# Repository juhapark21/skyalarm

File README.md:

# Sky Alarm
The sky alarm from xkcd #2979! It tells you when cool space things are happening. 

## Why 

I also wanted this device. There are alert apps and telegram groups and RSS feeds out there, but I wanted something not tied to my phone or computer. I also thought it would be fun to make a large physical device in the style of the original comic. 

## Features 
- Siren turns on (sound and light) when a cool space thing is happening in your location 
- Only alerts for phenomena observable with the naked eye 
- Cool space things:
  - Lunar eclipses
  - Solar eclipses
  - Supermoons
  - ISS passes
- Configurable notification settings 

## Usage 
2. Strip a cable (USB-C to USB-C or USB-A to USB-C; if using the latter, strip the USB-C end).
3. Locate the power and ground cables.
4. Secure the power and ground cables to their corresponding screw terminals (labeled on the PCB).
5. Get two lengths of wire. Connect one end of each wire to the battery terminals of the siren. (You may need to disassemble or drill into the casing to access this)
6. Connect the remaining end of each wire to the siren screw terminals (labeled on the PCB).
7. Put in separate batteries for the siren. Make sure the switch is turned ON.
8. Plug in any USB-C to USB-C wall charger to the XIAO ESP32C3.
9. Plug in the external power cable. 

## Specifications 
- XIAO ESP32C3 microcontroller - edit firmware without any extra equipment
- MAX98357A - cheap and widely available amplifier 
- Any toy siren ~5V with an on-off switch and batteries should work
- 61.4 x 65.5 mm PCB - casing can be made smaller with different parts without adjusting the board
- Runs on any wall power supply 1A-3A (suggested) 
- bom can be found as bom.csv 

## Upcoming features 
- Weather checks - no alerts if overcast
- Description page for details about alerted event 
- Custom audio 
- Switching from API calls to local calculations for more predictable events 
- More cool space things!

## Images 

## Credits 
Inspiration from [https://xkcd.com/2979/](https://xkcd.com/2979/) 

Font from [https://github.com/ipython/xkcd-font](https://github.com/ipython/xkcd-font)

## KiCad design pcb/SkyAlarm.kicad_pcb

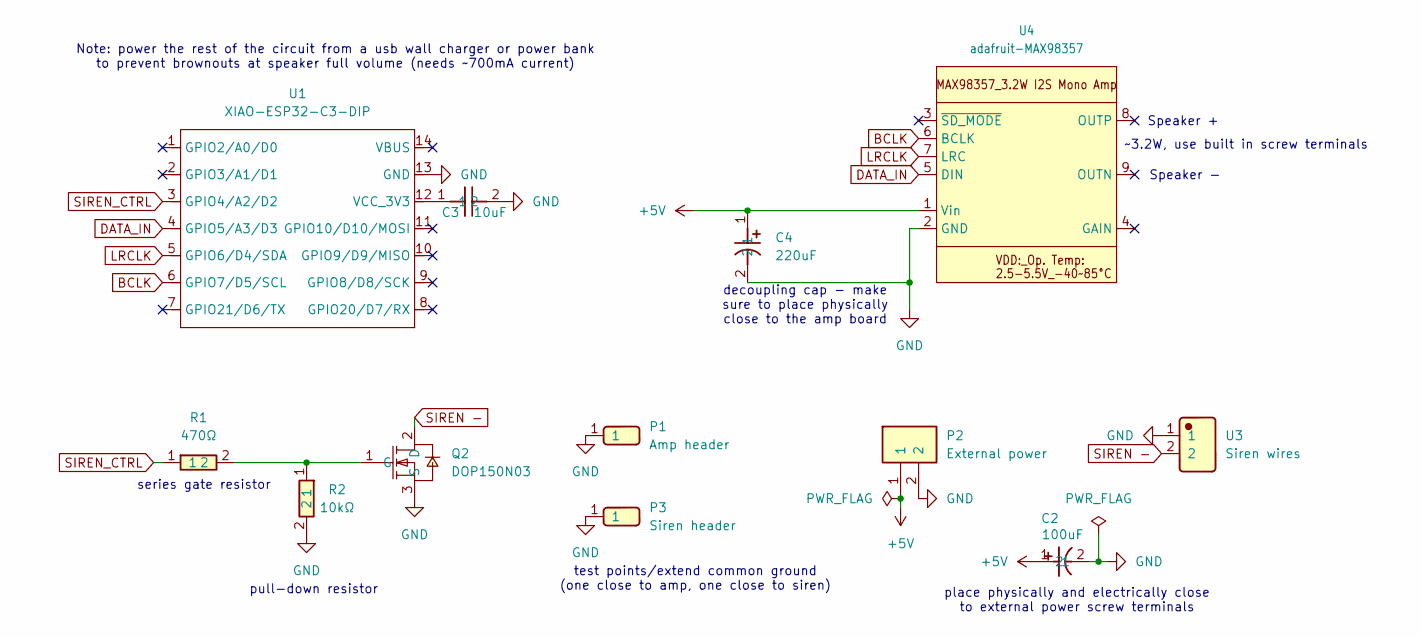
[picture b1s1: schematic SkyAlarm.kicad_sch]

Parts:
C2: 100uF; KS107M025E07RR0VH2FP0; Manufacturer Part KS107M025E07RR0VH2FP0; LCSC C44587
C3: 10uF; KTD350B106K43A0T00; Manufacturer Part KTD350B106K43A0T00; LCSC C32753248
C4: 220uF; ERG25V220M6X11; Manufacturer Part ERG25V220M6X11; LCSC C47344177
P1: Amp header; Header-Male-2_54_1x1; Manufacturer Part 2.54-1*1P针; LCSC C81276
P2: External power; WJ500V-5_08-2P-14-00A; Manufacturer Part WJ500V-5.08-2P; LCSC C8465
P3: Siren header; Header-Male-2_54_1x1; Manufacturer Part 2.54-1*1P针; LCSC C81276
Q2: DOP150N03; TO-220-3_L10.0-W4.5-P2.54-L-1; MPN DOP150N03; LCSC Part C42395896
R1: 470Ω; MF1_2WS-470_1_T52; Manufacturer Part MF1/2WS-470Ω±1% T; LCSC C129899
R2: 10kΩ; MF1_4W-10K_1_T52; Manufacturer Part MF1/4W-10KΩ±1% T; LCSC C119347
U1: XIAO-ESP32-C3-DIP; XIAO-ESP32C3-DIP
U3: Siren wires; DB301V-3_5-2P-GN; Manufacturer Part DB301V-3.5-2P-GN-S; LCSC C695629
U4: adafruit-MAX98357

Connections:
+5V: C2.1, C4.1, P2.1, U4.1 (Vin)
BCLK: U1.6 (GPIO7/D5/SCL), U4.6 (BCLK)
DATA_IN: U1.4 (GPIO5/A3/D3), U4.5 (DIN)
GND: C2.2, C3.2, C4.2, P1.1 (1_1), P2.2, P3.1 (1_1), Q2.3 (S), R2.2, U1.13 (GND), U3.1, U4.2 (GND)
LRCLK: U1.5 (GPIO6/D4/SDA), U4.7 (LRC)
unnamed: Q2.1 (G), R1.2, R2.1
unnamed: C3.1, U1.12 (VCC_3V3)
SIREN -: Q2.2 (D), U3.2
SIREN_CTRL: R1.1, U1.3 (GPIO4/A2/D2)

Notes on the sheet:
Note: power the rest of the circuit from a usb wall charger or power bank to prevent brownouts at speaker full volume (needs ~700mA current)
series gate resistor
pull-down resistor
~3.2W, use built in screw terminals
Speaker +
place physically and electrically close to external power screw terminals
decoupling cap - make sure to place physically close to the amp board
test points/extend common ground (one close to amp, one close to siren)
Speaker -

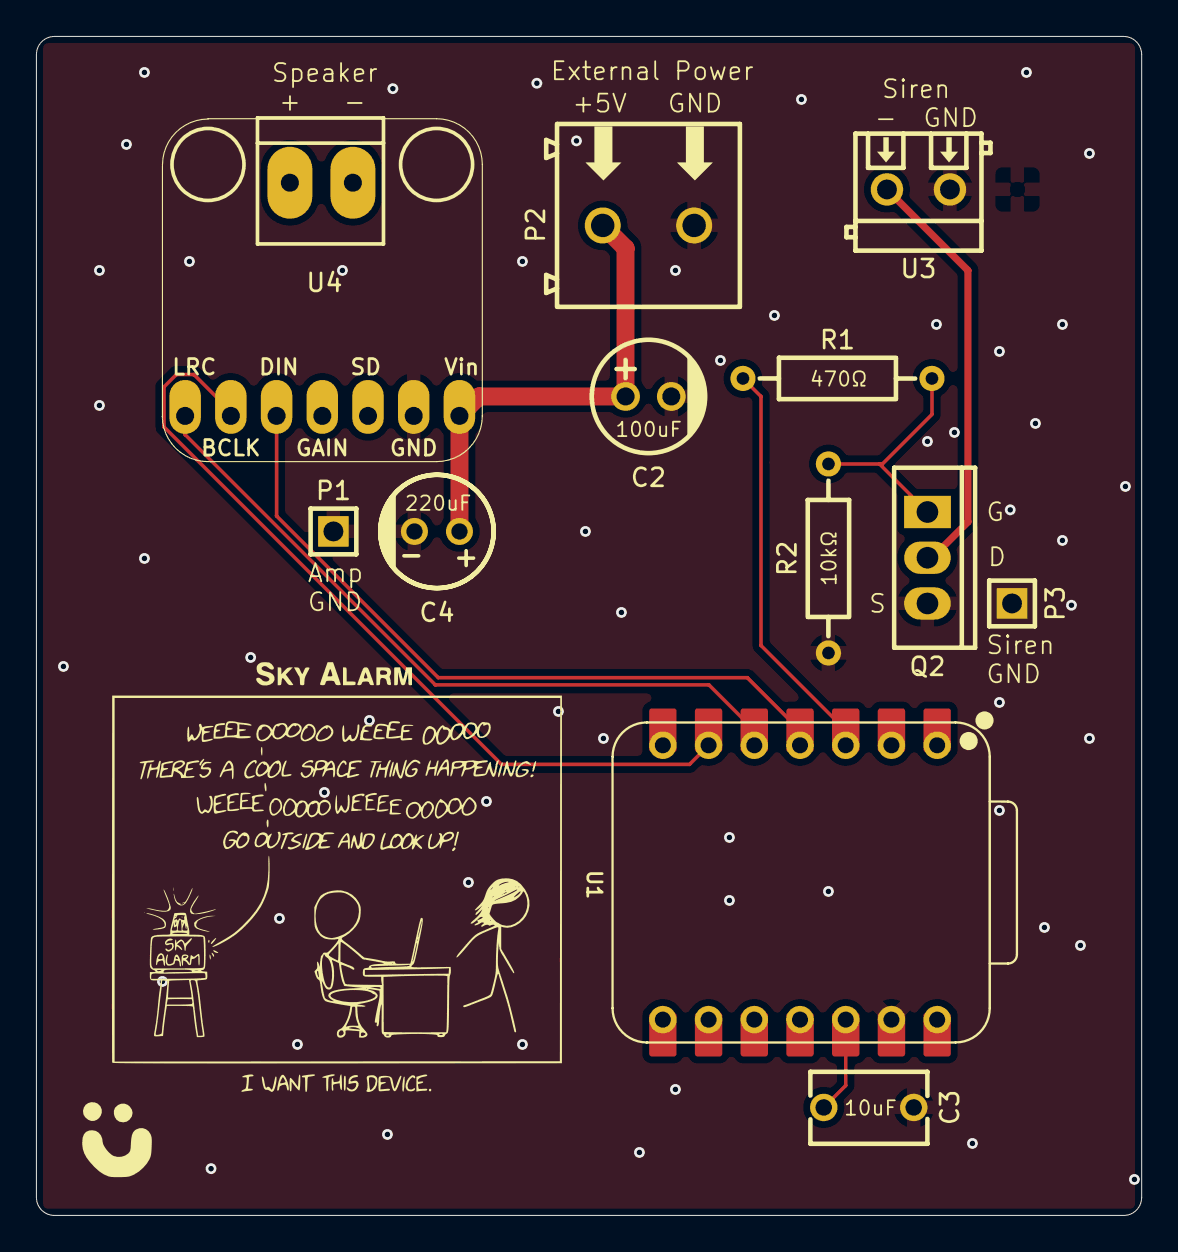
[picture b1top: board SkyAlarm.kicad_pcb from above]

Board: 2 copper layers, 61.4 x 65.5 mm, 12 parts (0 on the bottom side), 9 nets.

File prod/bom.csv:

Designator,Footprint,Quantity,Value,LCSC Part #
C2,KS107M025E07RR0VH2FP0,1,100uF,C44587
C3,KTD350B106K43A0T00,1,10uF,C32753248
C4,ERG25V220M6X11,1,220uF,C47344177
P1,Header-Male-2_54_1x1,1,Amp header,C81276
P2,WJ500V-5_08-2P-14-00A,1,External power,C8465
P3,Header-Male-2_54_1x1,1,Siren header,C81276
Q2,TO-220-3_L10.0-W4.5-P2.54-L-1,1,DOP150N03,C42395896
R1,MF1_2WS-470_1_T52,1,470Ω,C129899
R2,MF1_4W-10K_1_T52,1,10kΩ,C119347
U1,XIAO-ESP32C3-DIP,1,XIAO-ESP32-C3-DIP,
U3,DB301V-3_5-2P-GN,1,Siren wires,C695629
U4,adafruit-MAX98357,1,adafruit-MAX98357,
